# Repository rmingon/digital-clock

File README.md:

# Digital clock

## Just a digital clock with atmega328p + ws2812b + RTC

# FINISH

# ONE DIGIT -> [VIDEO](https://www.youtube.com/shorts/d32lipOYpTA)

# CHAINED DIGITS -> [VIDEO](https://www.youtube.com/shorts/P1QIr2BeblI)

# CLOCK ON WALL -> [VIDEO](https://www.youtube.com/shorts/ad-uJUUdQWM)

## How to program
### For use this clock you will need to program the mcu via ICSP. (USBASP for example)

## TODO 
- [x] add connector for multiple pcb
- [ ] add capacitor
- [ ] add more light ??
- [ ] ESP8266 ?

### Schematic

### PCB

### 3D Front

### 3D Back

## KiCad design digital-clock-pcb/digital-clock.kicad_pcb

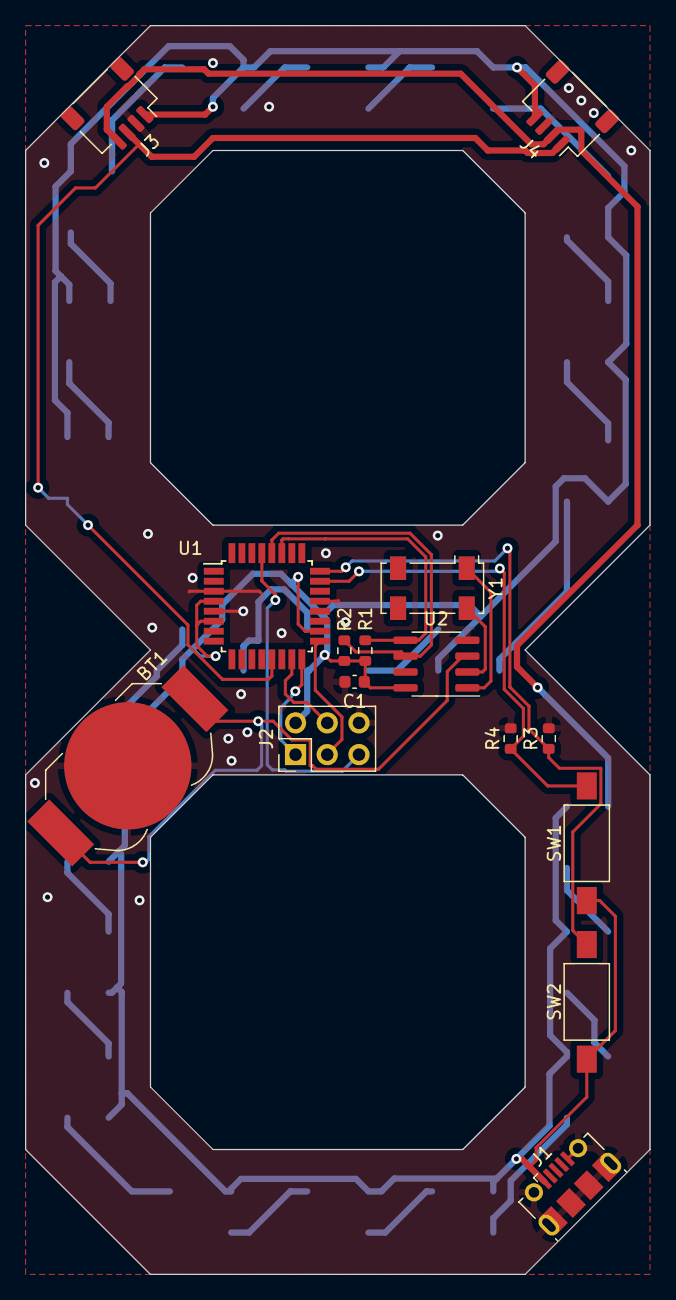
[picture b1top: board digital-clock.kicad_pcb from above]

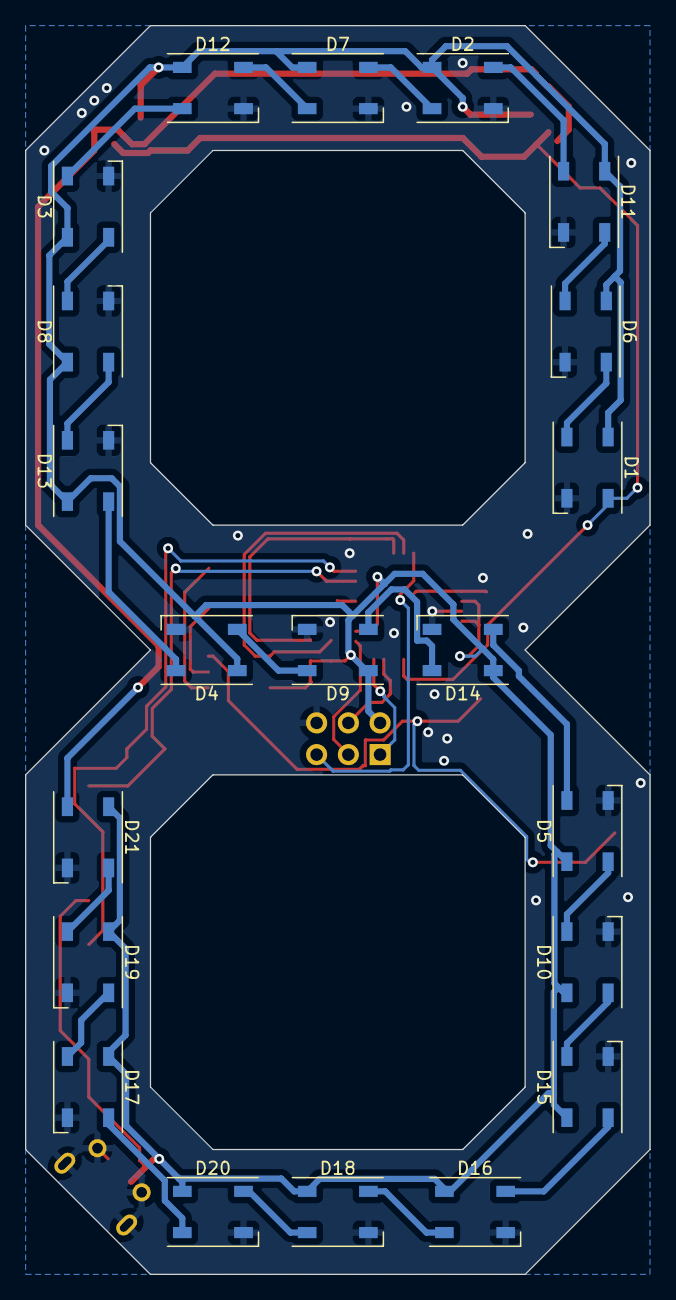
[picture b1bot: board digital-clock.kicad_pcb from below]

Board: 2 copper layers, 50.0 x 100.0 mm, 36 parts (21 on the bottom side), 35 nets.

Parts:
BT1: Battery_Cell; BatteryHolder_LINX_BAT-HLD-012-SMT
C1: C_Small; C_0603_1608Metric
D1, D2, D3, D4, D5, D6, D7, D8, D9, D10, D11, D12, D13, D14, D15, D16, D17, D18, D19, D20, D21: WS2812B; LED_WS2812B_PLCC4_5.0x5.0mm_P3.2mm
J1: USB_OTG; USB_Micro-B_Molex-105017-0001
J2: Conn_02x03_Odd_Even; PinHeader_2x03_P2.54mm_Vertical
J3, J4: Conn_01x04; JST_SH_SM04B-SRSS-TB_1x04-1MP_P1.00mm_Horizontal
R1, R2, R3, R4: R_Small; R_0603_1608Metric
SW1, SW2: SW_SPST; SW_SPST_FSMSM
U1: ATmega328P-M; TQFP-32_7x7mm_P0.8mm
U2: PCF8523T; SOIC-8_3.9x4.9mm_P1.27mm
Y1: ABS2532768KHZ6T; Crystal_SMD_Abracon_ABS25-4Pin_8.0x3.8mm

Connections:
BTN1: R4.1, SW1.2 (B), U1.23 (PC0)
BTN2: R3.1, SW2.2 (B), U1.24 (PC1)
GND: BT1.2 (-), C1.2, D1.3 (VSS), D2.3 (VSS), D3.3 (VSS), D4.3 (VSS), D5.3 (VSS), D6.3 (VSS), D7.3 (VSS), D8.3 (VSS), D9.3 (VSS), D10.3 (VSS), D11.3 (VSS), D12.3 (VSS), D13.3 (VSS), D14.3 (VSS), D15.3 (VSS), D16.3 (VSS), D17.3 (VSS), D18.3 (VSS), D19.3 (VSS), D20.3 (VSS), D21.3 (VSS), J1.5 (GND), J1.6 (Shield), J2.6, J3.2, J4.3, R3.2, R4.2, U1.3 (GND), U1.5 (GND), U1.21 (GND), U2.4 (VSS)
MISO: J2.1, U1.16 (PB4)
MOSI: J2.4, U1.15 (PB3)
unnamed: BT1.1 (+), U2.3 (VBAT)
unnamed: D1.2 (DOUT), D6.4 (DIN)
unnamed: D2.2 (DOUT), D7.4 (DIN)
unnamed: D3.2 (DOUT), D8.4 (DIN)
unnamed: D4.2 (DOUT), D9.4 (DIN)
unnamed: D5.2 (DOUT), D10.4 (DIN)
unnamed: D10.2 (DOUT), D15.4 (DIN)
unnamed: D6.2 (DOUT), D11.4 (DIN)
unnamed: D2.4 (DIN), D11.2 (DOUT)
unnamed: D7.2 (DOUT), D12.4 (DIN)
unnamed: D3.4 (DIN), D12.2 (DOUT)
unnamed: D8.2 (DOUT), D13.4 (DIN)
unnamed: D4.4 (DIN), D13.2 (DOUT)
unnamed: D9.2 (DOUT), D14.4 (DIN)
unnamed: D5.4 (DIN), D14.2 (DOUT)
unnamed: D15.2 (DOUT), D16.4 (DIN)
unnamed: D16.2 (DOUT), D18.4 (DIN)
unnamed: D17.4 (DIN), D20.2 (DOUT)
unnamed: D17.2 (DOUT), D19.4 (DIN)
unnamed: D18.2 (DOUT), D20.4 (DIN)
unnamed: D19.2 (DOUT), D21.4 (DIN)
unnamed: U2.1 (OSCI), Y1.1
unnamed: U2.2 (OSCO), Y1.4
RST: J2.5, U1.29 (~RESET/PC6)
SCK: J2.3, U1.17 (PB5)
SCL: R2.2, U1.28 (PC5), U2.6 (SCL)
SDA: R1.2, U1.27 (PC4), U2.5 (SDA)
VCC: C1.1, D1.1 (VDD), D2.1 (VDD), D3.1 (VDD), D4.1 (VDD), D5.1 (VDD), D6.1 (VDD), D7.1 (VDD), D8.1 (VDD), D9.1 (VDD), D10.1 (VDD), D11.1 (VDD), D12.1 (VDD), D13.1 (VDD), D14.1 (VDD), D15.1 (VDD), D16.1 (VDD), D17.1 (VDD), D18.1 (VDD), D19.1 (VDD), D20.1 (VDD), D21.1 (VDD), J1.1 (VBUS), J2.2, J3.1, J4.4, R1.1, R2.1, SW1.1 (A), SW2.1 (A), U1.4 (VCC), U1.6 (VCC), U1.18 (AVCC), U2.8 (VDD)
WS_IN: D1.4 (DIN), J3.3, J4.1, U1.13 (PB1)
WS_OUT: D21.2 (DOUT), J3.4, J4.2

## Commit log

2023-03-28 init project
2023-03-28 add README.md
2023-03-30 pictures
2023-03-30 add pcb
2023-03-30 up readme
2023-03-30 add how to program
2023-03-30 update silkscreen
2023-06-16 add connector
2023-06-16 wiring connector
2023-07-01 change m328 package
2023-07-15 add video to readme
2023-07-18 update view
2023-07-18 add clock battery + add button for change hour and minute
2023-08-23 add gnd usb
2023-08-23 add working clock video
2023-08-23 add finish picture
2023-08-23 add finish picture in readme
2023-08-23 add code platformio
2023-08-25 update code
2023-08-25 update pcb
